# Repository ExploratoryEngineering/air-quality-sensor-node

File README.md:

# Air quality sensor node

(work in progress)

GPS enabled NB-IoT Sensor node for sampling NO2, NO, O3 and particulate matter.

## OPC-N3 particle sensor

## AFE-3 Analog frontend for NO2, NO and O3 electrochemical sensors

## Vehicle power board

## EE-NBIoT-02 module

## Controller board with nrf52, GPS and ADC

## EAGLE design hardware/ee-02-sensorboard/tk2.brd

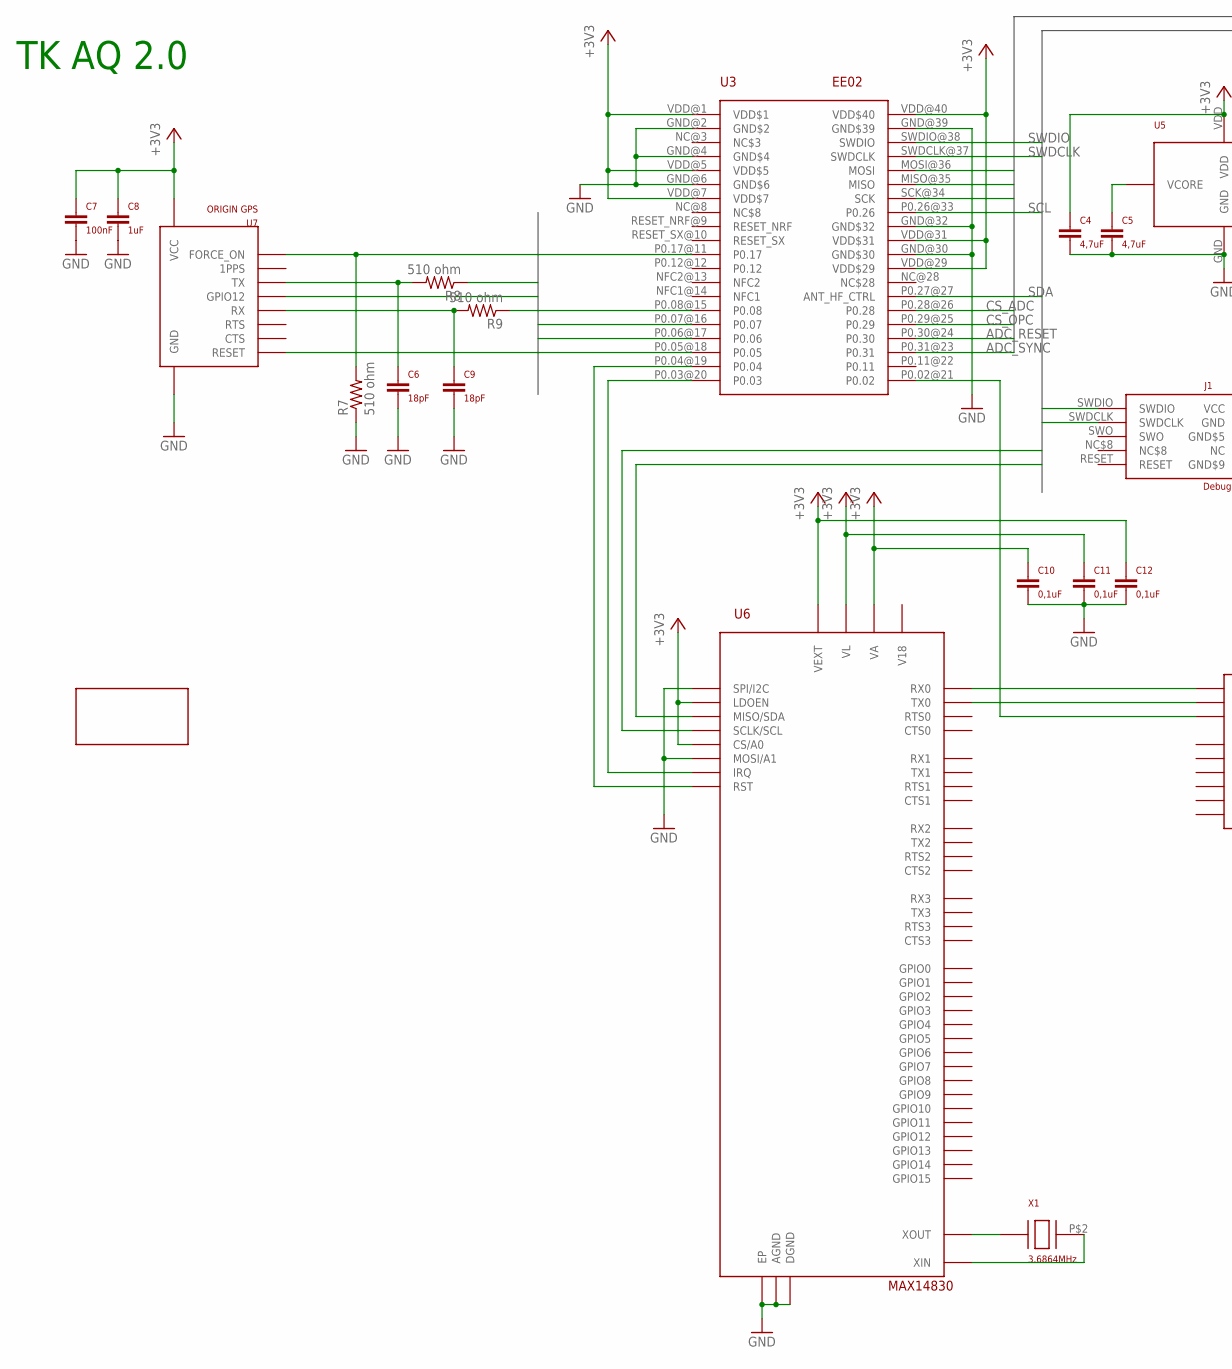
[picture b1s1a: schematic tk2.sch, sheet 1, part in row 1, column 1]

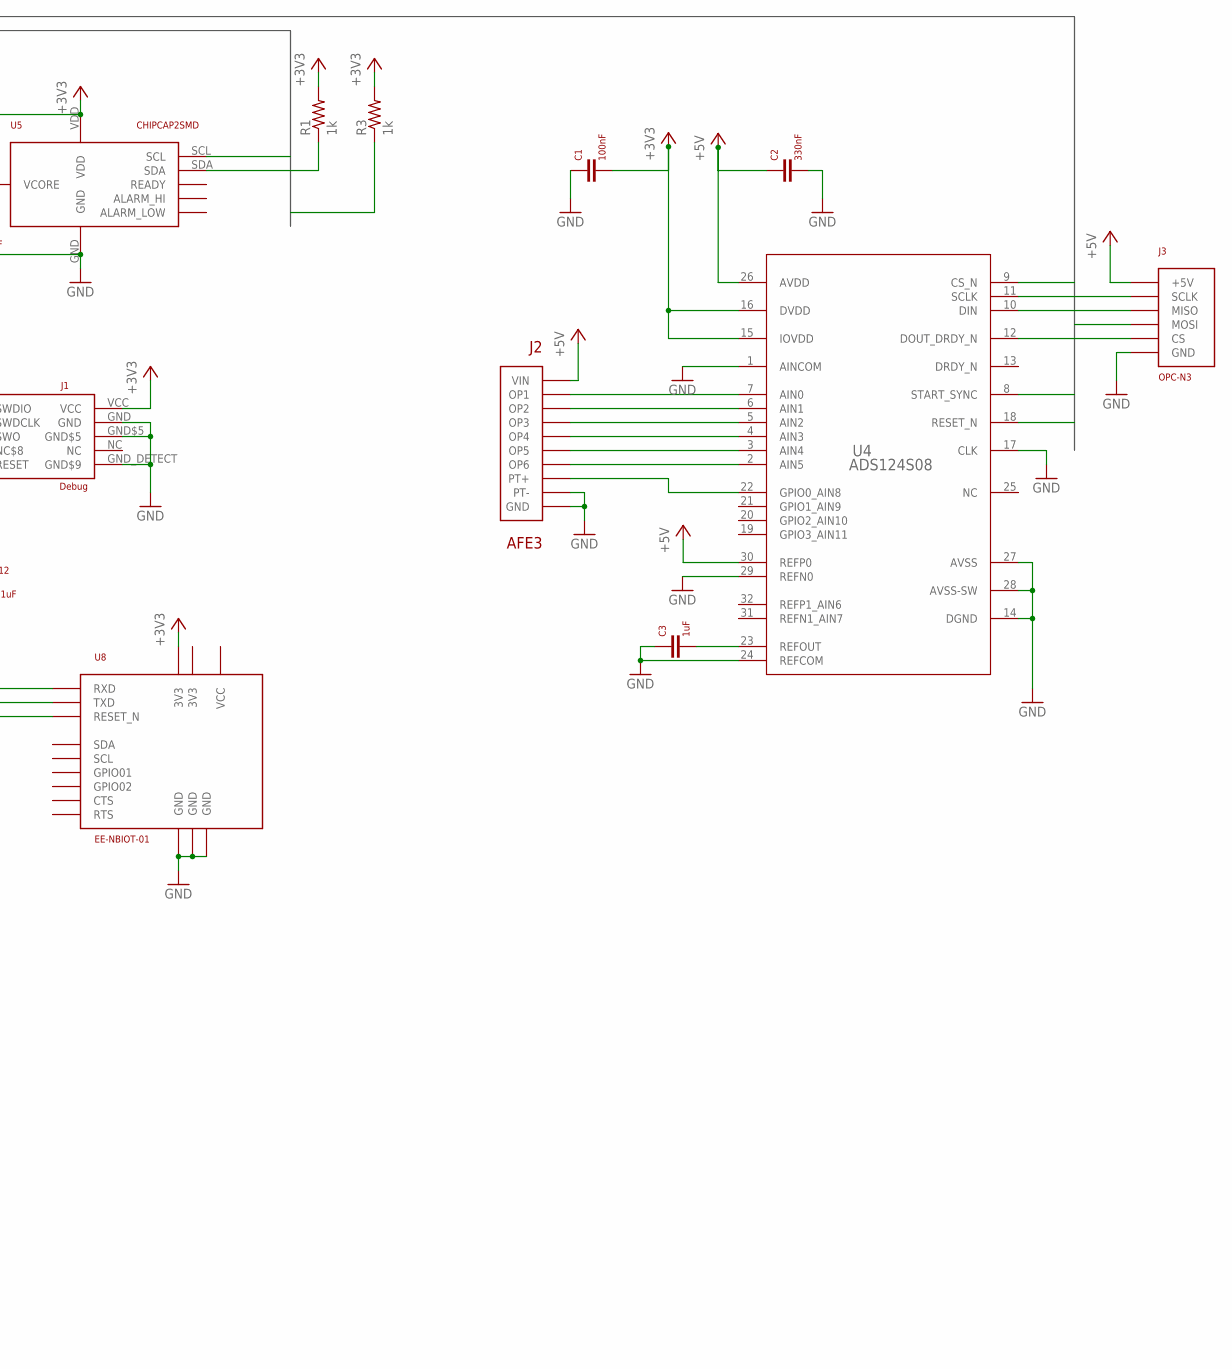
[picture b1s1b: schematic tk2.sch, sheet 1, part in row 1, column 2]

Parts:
C1: 100nF; 0402
C2: 330nF; 0402
C3: 1uF; 0402
C4, C5: 4,7uF; 0805
C6, C9: 18pF; 0805
C7: 100nF; 0805
C8: 1uF; 0805
C10, C11, C12: 0,1uF; 0805
J1: Debug; NRF52-P19-CONNECTOR
J2: AFE3_IDC_CABLE
J3: OPC_N3_CONNECTOR
R1, R3: 1k; 0805
R7, R8, R9: 510 ohm; 0805
U3: EE02; EE02_02
U4: ADS124S08; PBS0032A_N
U5: CHIPCAP2SMD; CHIPCAP2
U6: MAX14830
U7: ORIGIN GPS; ORIGIN_GPS_HORNET_1510
U8: EE-NBIOT-01
U$1: EE_TK_LOGO
X1: CRYSTAL_HC49

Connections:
+3V3: C1.2, C4.1, C7.1, C8.1, C10.1, C11.1, C12.1, J1.VCC, R1.2, R3.2, U3.VDD@1 (VDD$1), U3.VDD@5 (VDD$5), U3.VDD@7 (VDD$7), U3.VDD@29 (VDD$29), U3.VDD@31 (VDD$31), U3.VDD@40 (VDD$40), U4.15 (IOVDD), U4.16 (DVDD), U5.VDD, U6.CS/A0, U6.LDOEN, U6.VA, U6.VEXT, U6.VL, U7.4_VCC (VCC), U8.3V3@3 (3V3); also elsewhere on the board
+5V: C2.1, J2.VIN, J3.+5V, U4.26 (AVDD), U4.30 (REFP0); also elsewhere on the board
ADC_RESET: U3.P0.30@24 (P0.30), U4.18 (RESET_N)
ADC_SYNC: U3.P0.31@23 (P0.31), U4.8 (START_SYNC)
CS_ADC: U3.P0.28@26 (P0.28), U4.9 (CS_N)
CS_OPC: J3.CS, U3.P0.29@25 (P0.29)
FORCE_ON: R7.2, U3.P0.17@11 (P0.17), U7.1_FORCE_ON (FORCE_ON)
GND: C1.1, C2.2, C3.1, C4.2, C5.2, C6.2, C7.2, C8.2, C9.2, C10.2, C11.2, C12.2, J1.GND, J1.GND$5, J1.GND_DETECT (GND$9), J2.GND, J2.PT-, J3.GND, R7.1, U3.GND@2 (GND$2), U3.GND@4 (GND$4), U3.GND@6 (GND$6), U3.GND@30 (GND$30), U3.GND@32 (GND$32), U3.GND@39 (GND$39), U4.1 (AINCOM), U4.14 (DGND), U4.17 (CLK), U4.24 (REFCOM), U4.27 (AVSS), U4.28 (AVSS-SW), U4.29 (REFN0), U5.GND, U6.AGND, U6.DGND, U6.EP, U6.MOSI/A1, U6.SPI/I2C, U7.5_GND (GND), U8.GND@2 (GND), U8.GND@5 (GND), U8.GND@6 (GND); also elsewhere on the board
MISO: J3.MISO, U3.MISO@35 (MISO), U4.12 (DOUT_DRDY_N)
MOSI: J3.MOSI, U3.MOSI@36 (MOSI), U4.10 (DIN)
unnamed: C5.1, U5.VCORE
unnamed: C3.2, U4.23 (REFOUT)
unnamed: U6.RX0, U8.RXD
unnamed: U6.TX0, U8.TXD
unnamed: C6.1, R8.2, U7.3_TX (TX)
unnamed: C9.1, R9.2, U7.10_RX (RX)
unnamed: J2.OP1, U4.7 (AIN0)
unnamed: J2.OP2, U4.6 (AIN1)
unnamed: J2.OP3, U4.5 (AIN2)
unnamed: J2.OP4, U4.4 (AIN3)
unnamed: U3.P0.03@20 (P0.03), U6.IRQ
unnamed: U3.P0.04@19 (P0.04), U6.RST
unnamed: U3.P0.02@21 (P0.02), U8.RESET_N
unnamed: U6.XOUT, X1.P$1
unnamed: U6.XIN, X1.P$2
unnamed: J2.OP5, U4.3 (AIN4)
unnamed: J2.OP6, U4.2 (AIN5)
unnamed: J2.PT+, U4.22 (GPIO0_AIN8)
RESET: U3.P0.06@17 (P0.06), U7.8_RESET (RESET)
RX: R9.1, U3.P0.07@16 (P0.07)
SCL: R1.1, U3.P0.26@33 (P0.26), U5.SCL, U6.SCLK/SCL
SCLK: J3.SCLK, U3.SCK@34 (SCK), U4.11 (SCLK)
SDA: R3.1, U3.P0.27@27 (ANT_HF_CTRL), U5.SDA, U6.MISO/SDA
SWDCLK: J1.SWDCLK, U3.SWDCLK@37 (SWDCLK)
SWDIO: J1.SWDIO, U3.SWDIO@38 (SWDIO)
TX: R8.1, U3.P0.08@15 (P0.08)
WAKE_UP: U3.P0.05@18 (P0.05), U7.6_GPIO12 (GPIO12)

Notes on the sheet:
TK AQ 2.0

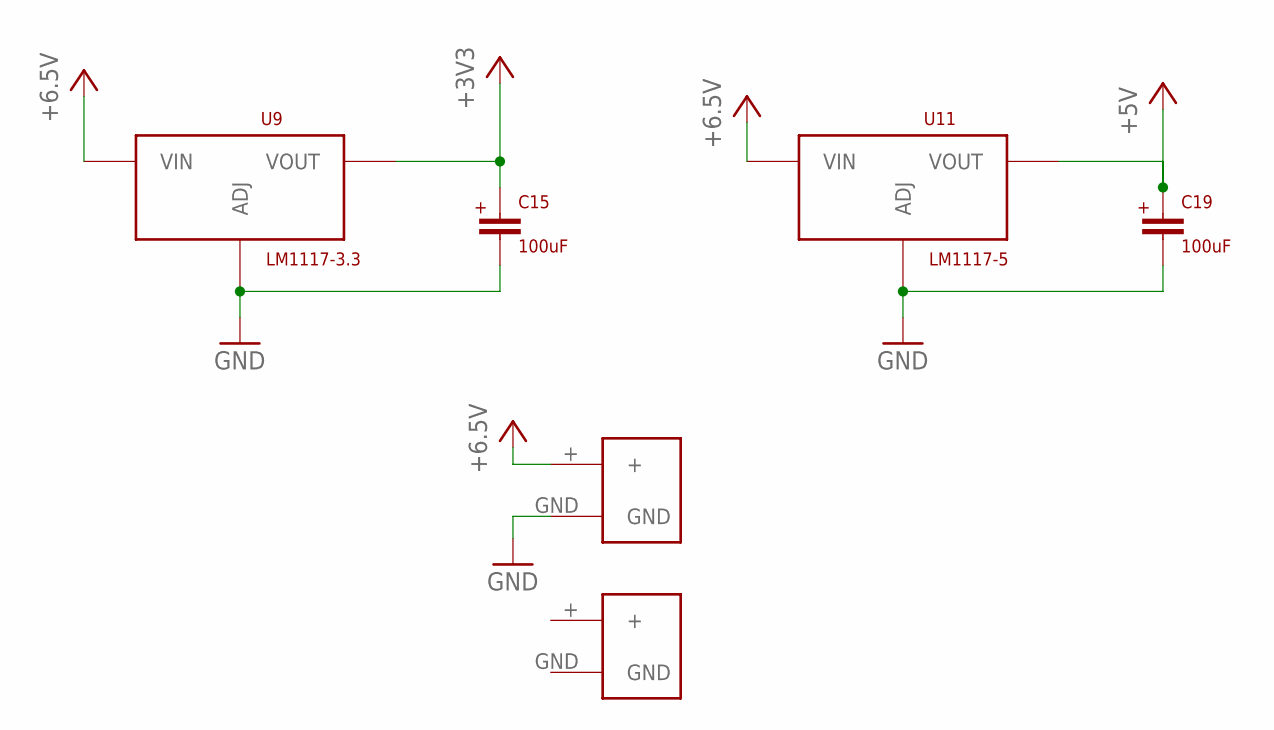
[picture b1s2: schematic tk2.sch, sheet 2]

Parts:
C15, C19: 100uF; ALUMINUM_WURTH_100UF_865080243007
U9: LM1117-3.3; LM1117
U11: LM1117-5; LM1117
U$2, U$3: PHOENIX_CONTACT_MSTBVA_2_5

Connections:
+3V3: C15.+, U9.VOUT$1 (VOUT), U9.VOUT$2 (VOUT); also elsewhere on the board
+5V: C19.+, U11.VOUT$1 (VOUT), U11.VOUT$2 (VOUT); also elsewhere on the board
+6.5V: U9.VIN, U11.VIN, U$2.+
GND: C15.-, C19.-, U9.GND (ADJ), U11.GND (ADJ), U$2.GND; also elsewhere on the board

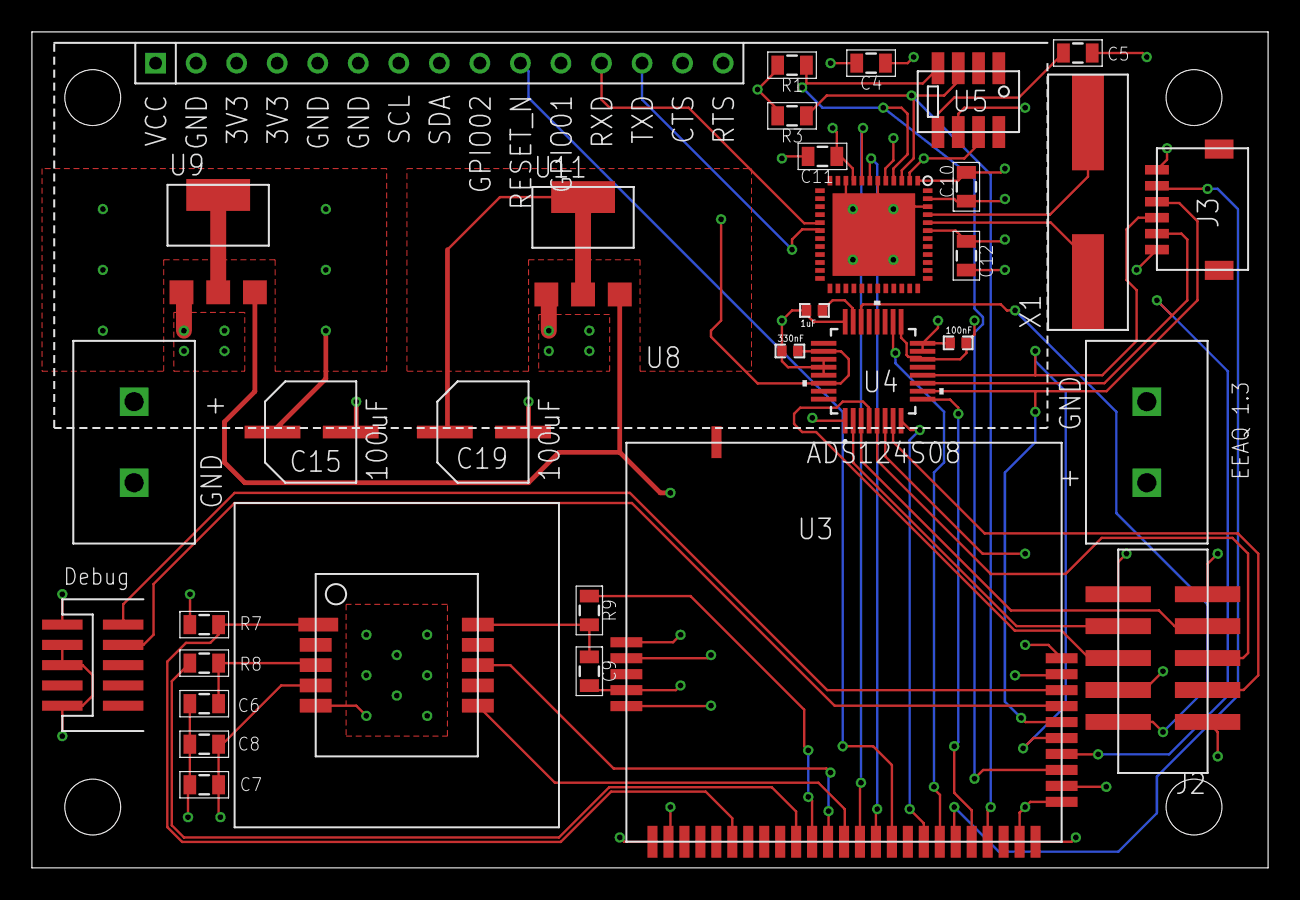
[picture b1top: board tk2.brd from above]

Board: 4 copper layers, 77.5 x 52.4 mm, 34 parts (1 on the bottom side), 38 nets.

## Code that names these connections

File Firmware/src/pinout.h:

/*
**   Copyright 2020 Telenor Digital AS
**
**  Licensed under the Apache License, Version 2.0 (the "License");
**  you may not use this file except in compliance with the License.
**  You may obtain a copy of the License at
**
**      http://www.apache.org/licenses/LICENSE-2.0
**
**  Unless required by applicable law or agreed to in writing, software
**  distributed under the License is distributed on an "AS IS" BASIS,
**  WITHOUT WARRANTIES OR CONDITIONS OF ANY KIND, either express or implied.
**  See the License for the specific language governing permissions and
**  limitations under the License.
*/

#ifndef _PINOUT_H_
#define _PINOUT_H_

#define CS_ADC  28
#define CS_OPC  29
#define CS_SX1276 22

#define ADC_RESET 30
#define ADC_SYNC 31

#define GPS_FORCE_ON    17
#define GPS_TX          8
#define GPS_RX          07
#define GPS_RESET       6
#define GPS_WAKE_UP     5

#define MAX14830_IRQ    3
#define MAX14830_RESET  4

#define EE_NBIOT_01_RESET 2

#endif

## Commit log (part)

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2020-01-13 Hardware verification
    * Verified ADC SPI driver
    * verified CC2 driver
    * ported GPS code to zephyr
    * verified OPC-N3 communication
    * All I2C devices responds (still have to port the MAX14830 driver)
2020-01-13 Added images of the electronics
2020-01-13 Added a README
    and some images of the sensor node electronics
2020-01-14 Added step files for PCB stack
2020-01-14 Added hardware design files
2020-01-16 Added preliminary renders
2020-01-16 Added enclosure README
2020-01-16 Updated image links
2020-01-23 Uart multiplexer / buffer is now working in polled mode in zephyr * removed txrxbuffer.h/.c * fixed max14830 reset sequence * renamed stuff in i2c/spi config * added EE_NBIOT_01_RESET to gpio initial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
2020-01-24 Added assembly for sensor innards
2020-01-29 Functional ADS124S08 driver
2020-01-30 Added STEP files for air nozzles
2020-01-30 Corrected CS pin for OPC-N3 * CC2/OPC/ADC now running in main thread * Added messagebuffer * Removed redundant log messages
2020-02-04 Zephyr 2.1.0, FOTA, socket offloading
    Add necessary import and clean up prj.conf. Moved nRF5x options
    into boards/nrf52_pca10040.conf.
    Add versioning via Reto (config is TBD).
2020-02-04 Various cleanups
    Change printk -> printf
    Disable format overflow warning in n2_offload.c
2020-02-04 Move max14830 thread from main to max14830 source
    Keep thread declaration and creation with rest of code. The thread is now
    created when the semaphore is available so it's launched ASAP.
2020-02-04 Integrate max14830 and comms from n2 offload
2020-02-04 Cleanups and reorgs
    * Get rid of "extern ..." (mostly)
    * Log names
    * .gitignore
    * Get rid of config.h
    * Get rid of fota_uart_* (not used)
    * Clean up main
2020-02-04 Move code around
2020-02-05 First integration
    Fun fact: SPI can't be initialised from the network offloading function
    for reasons unknown.
2020-02-06 Update Makefile and README
2020-02-06 Include board when building MCUBoot
2020-02-06 Update README with message format
2020-02-06 Configure modem on startup
    Set APN to mda.ee and autoconnect to true.
    Also wait for the inital OK from the modem when it is powered up.
2020-02-06 Make semaphore for FOTA reboots
    Let the FOTA process run while data is sent. It should work.
    When there's time to reboot the semaphore is grabbed by the FOTA process
    and sampling will stop.
2020-02-07 Simple FOTA WIP, including head scratching process.
2020-02-10 Updated and renamed sensor block
2020-02-10 Debugging Max 14830
    It seems to get a small stroke when the input buffer is 128 bytes
2020-02-10 Hack for NSORF and MAX/SARA troubles, CoAP tokens
    Somewhere between the SARA N2 UART and the MAX-something chip there's
    some interesting interaction so the final OK for the NSORF is dropped.
    Stop processing when data is received and ignore the rest of the input.
    Also use secure random CoAP tokens.
2020-02-12 CMakeFile: Set current directory to absolute path
    Also print messages when building
2020-02-13 I'm considering libcoap at this point in time
2020-02-13 Enable regular sampling
2020-02-13 Remove sleep loop
    Turns out sleeping forever won't get you much sampling.
    Go figure.
2020-02-13 Dump mega buffer when writing NSOST
    Also turn of chatty logging for (almost complete) modules.
2020-02-14 Use polling for max14830
2020-02-17 Firmware download + write to flash
    Note: It's commented out for main.
2020-02-17 Timeout on firmware download.
    Note: There's no retry on send.
2020-02-17 Bump version, update changelog
2020-02-17 Remove limit for block count
2020-02-17 Clean up FOTA code
2020-02-24 Added uptime field to message
2020-02-26 First commit. Tool for listening to data from device.
2020-03-02 Implemented airplane mode...
2020-03-02 Format data as hex array
2020-03-02 Spit out JSON format as well for the aqfetch tool
2020-03-02 Renamed things a bit
2020-03-03 Added protobuffer definition
2020-03-03 Added protobuffer to build
2020-03-03 Fixed initialization of CC2 sensor * added missing OPC humidity field to message * added message hex dump (debug) output
2020-03-04 Modified how bins are handled and removed nanopb.proto
2020-03-05 Closed a few sockets.
2020-03-05 Updated listener to use protobuffer. Started work on server
2020-03-06 Set version to 0.1.0 and supressed output from protobuf generation
2020-03-06 Change #include to support case sensitive FS
2020-03-06 Ignore external deps added by west update
2020-03-06 Start using west for dependencies and zephyr
    From now on, this repo will have it's own copy of zephyr
    to make it easier for everyone. If you want to change the
    version of zephyr (or any other deps, update the manifest).
2020-03-06 Update compile / build instructions and requirements
2020-03-06 Use mcuboot fetched with west update
2020-03-06 WIP: trying to figure out why protobuf doesn't work
2020-03-06 Ahem
2020-03-06 Added to README.md
2020-03-06 Added some documentation on how to install prerequisites
2020-03-06 Last change of protobuf where we renumber
2020-03-06 Now transmitting protobuffer instead of old byte buffer
2020-03-07 Work on listener and pipeline
2020-03-07 Oops, that binary shouldn't have been there and it shouldn't have been checked in
2020-03-07 Removed codec package which is no longer needed
2020-03-08 WIP working on pkg/store
2020-03-08 More work on persistence layer
2020-03-09 Reverted to older protobuf version for now
2020-03-09 Added sensor calculations
2020-03-15 WIP calc stuff
2020-03-16 Some updates to model and calculation
2020-03-16 Added systemID and 64 bit representation of fw version to message
2020-03-17 Testing FOTA
2020-03-18 Shortened some names and clarified others
2020-03-18 Fixed a bug in fota.c that prevented reboot * Fixed a bug in target definition * Changed logging level from warning to error for two fota messages
2020-03-19 Removed redundant log messages from messagebuffer
2020-03-19 Release 0.0.12
    Released version 0.0.12 (lethal-dani)
2020-03-19 Getting ready for pipeline test
2020-03-20 Added calibration data
2020-03-23 Work on cal utility and schema and naming
2020-03-23 Added list, rm, import to cal utility
2020-03-23 Convenience script for importing calibration data
2020-03-23 Added CollectionID to cal data
2020-03-23 Say when there are no cal entries to list so the user sees some output
2020-03-24 Added JSON formatting to cal show, reverted mistake (use device IDs instead of entry ids)
2020-03-24 Added first rudimentary version of calculate pipeline element
2020-03-29 Tied together pipeline code and added calibration - Removed some of the noisy output
2020-04-03 Make calculated values in database nullable
2020-04-03 Consolidated cal and server binaries into aq
2020-04-03 Updated import script
2020-04-04 Added calibration data as JSON
    This is the format we support for distribution and only JSON files
    that have a valid device ID (Horde id) should be added here.
2020-04-04 Conversion sets CollectionID and ValidFrom
2020-04-04 Rearranged import a bit
2020-04-05 Initial version of fetching of backlog data from Horde
    This will create duplicates if run more than once. Make sure you
    import the calibration data before you fetch data - the data is run
    through the processing pipeline where fields are calculated.
2020-04-11 Only fetch new messages. Also changed storage of Received timestamp to BIGINT
2020-04-12 Removed xCommand variables to enforce correct use
2020-04-26 Made some changes to proto generaiton to make it work on Linux
2020-04-26 Statred documentation
2020-04-26 Regenerated protobuffer
2020-04-26 Ignore all database files
2020-04-26 Calibration data is now downloaded from S3 bucket on startup and then every 12 hours
2020-04-27 Added comment for how far back we fetch data
2020-04-27 Refresh cache logic redone
2020-04-27 Added new calibration data
2020-04-27 Moving functionality to cal utility
2020-04-27 re-added DeviceID after mistaken update (rest of cal files lack device id though)
2020-05-06 Fixed mapping of temp in messagebuf
2020-05-06 Added STEP and STL files for PLA/PP parts
2020-05-12 Updated calibration data with device IDs, removed excel, csv, and scans
2020-05-15 Documentation updates
2020-05-16 Added Websocket message stream and circular buffer
2020-05-18 Fixed inconsistencies in storage
2020-05-18 Reorganized pipeline packages
2020-05-18 Added support for listing clients, shown as count on webpage
2020-05-18 Added logging and params for certs
2020-05-19 Count message drops
2020-06-29 Use CoAP to send data
2020-06-29 Fixed bug
2020-06-29 Updated message format information Previous versions used just raw C-structs, but since this is fragile when things change we switched to protobuffers.
2020-06-29 Path fix
2020-06-29 Giving up trying to make relative path work in links :)
2020-07-07 Added simple example of MQTT forwarding
2020-07-14 Put horde and udp listener in their own packages
2020-07-14 Adding calibration data
2020-07-14 Renamed calibration data files
2020-07-14 Added preliminary MIC support to AQ
    Added preliminary MIC support to AQ. Note that MIC doesn't send us any metadata
    with our payload so we have to depend entirely on the payload from the device.
    Fortunately we can fix this by utilizing the sysid to uniquely identify the devices
    and look up the calibration data.
    Also included the calibration data in the repository since having to maintain
    an S3 bucket is not going to work as a long term solution.
2020-07-15 Fixed typo
2020-07-23 feat: add fetch from MIC Elasticsearch
2020-07-23 chore: remove unnecessary const's
2020-08-19 Version update
2020-08-19 Added code to read calibration data from files locally
2020-08-20 Changed the way calibration data is handled.
    Rather than distributing the calibration data via AWS S3 we will now
    be distributing it by putting it in Github. This means that anyone operating
    an AQ server has to be a bit on their toes about updating the data themselves
    but it removes the burden of maintaining the calibration data from Telenor.
    On startup the AQ server will look for calibration data in the directory
    specified by the -m or --cal-data-dir command line options. By default this
2020-09-03 Renamed some types so we can make them private and changed some error handling
2020-09-03 Added configuration options with defaults
2020-09-03 Renamed fetch-mic to fetch so that aq will now fetch from MIC. fetch-span must be used to fetch from nbiot.engineering
2020-09-25 NVS Storage and command protocol - part I
    * added initial version of config.proto for command protocol
    * added nanopb_generate for config-photo to CMakeLists.txt
    * fixed bug in makefile for target build_mcuboot
    * added watchdog
    * added non volatile storage of APN and COAP parameters
    * Fixed logging error in comms.c
2020-09-26 Implemnted two remote config commands * Set APN List command * Reboot command
2020-09-28 Removed unnecessary comment
2020-09-28 Implemented flash storage of COAP params
    * Increased HEAP size and SACK size
    * COAP parameters are now selected form NVS
    * Fixed a bug in decoding of protobuf config messages
2020-09-29 Now using protobufs with fixed array sizes
2020-09-29 Minor bugfixes * Added a missing sys_reboot() * Increased timeouts for IP * Updated default APN list
2020-09-30 Regenerated proto
2020-09-30 Last minute hack
    * prepending binary COAP header - don't ask
2020-09-30 Updated .gitignore
2020-10-01 removed unnecessary reboot
2020-10-06 Added float fields for PM1, PM2.5 og PM10
2020-10-07 index on master: 5ae065f Updated .gitignore
2020-10-07 Regenerated protobuffer code for Go
2020-10-07 Re-set command line options to what it was before ES-integration
2020-10-07 Changed command line parameters back
2020-10-08 Removed unneeded templates and static dir serving
2020-10-08 Fixed PING encoding
    * added PM1,PM2.5 and PM10 fields (decimal) to message
2020-10-29 Increased OPC sampling time to 30 seconds
2021-02-19 Added calibration data for 5 additional sensors
